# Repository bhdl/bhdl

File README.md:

# Board HDL: A Programming Language and System for making PCBs

Documents can be found at https://bhdl.org

This project is currently developed on a new IDE called CodePod, which is not publicly available yet. The `src` folder here is exported from CodePod IDE. We're working on making CodePod available for the general public. Issues are being tracked in this repo.

BHDL is a programming language embedded in
[racket](https://racket-lang.org/). In addition to the language, the system
consists of a layout co-design system based on functional picture, REPL-driven
interactive development and visualization, libraries, KiCAD compatible exporter,
and placement engines including an optimization-based anlytical placer (ePlace)
and simulated annealing based detailed placer.

# Setup

## Install Racket

Install [racket](https://racket-lang.org/):

```sh
apt install racket
```

On MacOS and Windows, you can [download the installer from the Racket website](https://download.racket-lang.org/), and setup
the commandline properly.

<!-- IMPORTANT: racket v7.8 seems to be broken! The cc-find will return negative values. That's apparently a bug of either racket v7.8 or the bundled pict library. Use v7.7 instead. Links to the download pages:

- [all versions](https://download.racket-lang.org/all-versions.html)
- [v7.7](https://download.racket-lang.org/racket-v7.7.html) -->

## Install BHDL package

Step 2: Install the BHDL directly as a racket package:

```
raco pkg install --auto https://github.com/bhdl/bhdl.git?path=src
```

You can now run racket and require bhdl. The first time requiring bhdl, it will download footprint library to `~/.config/bhdl/bhdl-footprints` (Linux) or `~/Library/Application Support/bhdl/bhdl-footprints` (MacOS).

```racket
racket
> (require bhdl)
```

Then try some of the [examples](/examples).

## Update BHDL

In the future, you can update the package if there're updates upstream via:

```shell
raco pkg update src
```

> note TODO package name should be `bhdl`

## JupyterLab IDE

In general, you can run racket programs via command line, editor plugins, IDEs. We are not covering them here. Instead, we recommand run the program via jupyter notebook. To set it up, first install jupyter:

```shell
pip install jupyterlab
```

The [iracket](https://github.com/rmculpepper/iracket) kernel requires on libzeromq:

```shell
sudo apt install libzmq5
```

> note for MacOS

> On MacOS, it is a little [trickier](https://github.com/rmculpepper/racket-zeromq/issues/6) to setup libzmq. Specifically, you need to copy the library to the racket's library path, otherwise racket won't find it:

> ```shell
> brew install zmq
> cp /opt/homebrew/Cellar/zeromq/4.3.4/lib/libzmq.5.dylib Library/Racket/8.2/lib
> ```

Then install the kernel itself:

```shell
raco pkg install iracket
raco iracket install
```

> note:
> iracket does not allow write access to file system by default. So you have to
> modify the kernel file with a [`-t`
> parameter](https://github.com/rmculpepper/iracket/issues/13). In short, you need
> to modify the content of `~/.local/share/jupyter/kernels/racket/kernel.json` on
> your system from `["racket","-l","iracket/iracket","--","{connection_file}"]` to
> `["racket","-l","iracket/iracket","--","-t","{connection_file}"]`

Then start the jupyterlab server:

```shell
jupyter lab
```

You'll be able to create racket notebooks in the JupyterLab IDE. Inside the
notebook, try `(require bhdl)` and some of [the exampels](/examples).

<!-- TODO rename fitboard to BHDL-Key -->

<!-- - [BHDL-Key](bhdl-test/fitboard.ipynb): an ergonomic keyboard
- [onebutton](bhdl-test/onebutton.ipynb): a pushbutton board: https://github.com/forrestbao/onebutton
- [Arduino Spreadboard](bhdl-test/spreadboard.ipynb): an multi-dock for different form-factor Arduinos -->

<!-- One caveat to notice: the iRacket kernel seems to have problem when "restarting the kernel". The walk-around is to "shutdown the kernel" and "start it again". -->

## Placement (Optional)

To run the placement engine, you need setup
[julia](https://julialang.org/). Refer to their installation guide on how to
install Julia.

Install the BHDL julia package:

```
julia
]add https://github.com/bhdl/bhdl
```

Then run the server:

```
import BHDL
BHDL.web_server()
```

This will listen on `http://0.0.0.0:8082`. To use this, in racket, set the
parameter `placer-url`, and call `circuit-export` with `#:auto-place #t`:

```racket
;; set placer url
(placer-url "http://0.0.0.0:8082")
(circuit-export three-button #:auto-place #t ...)
```

This package will detect if Nvidia GPU is available, and use it if possible. The
first time invoking the package, julia will download and instantiate the
dependencies and download CUDA (julia will not use your system's CUDA setup).
The first time the placement is running, Julia will pre-compile the code, thus
maybe a little slower. Subsequent placement request will be much faster (which
is why we use a server instead of invoking the command for every placement request).

## Freerouting (Optional)

To use routing, you need to have
[freerouting](https://github.com/freerouting/freerouting) available. We tested
on
[freerouting-v1.4.4](https://github.com/freerouting/freerouting/releases/tag/v1.4.4). Make
sure `freerouting-1.4.4-executable.jar` is available in your `$PATH`.

The executable can be downloaded [here](https://bintray.com/miho/Freerouting/download_file?file_path=eu%2Fmihosoft%2Ffreerouting%2Ffreerouting%2F1.4.4%2Ffreerouting-1.4.4-executable.jar) on the new freerouting maintainer website: https://freerouting.mihosoft.eu/

UPDATE: the jar file is often not an executable command. You'll need

```
java -jar freerouting-1.4.4-executable.jar
```

Thus, you need to create a executable called `freerouting`, containing:

```
#!/bin/bash
java -jar /path/to/freerouting-1.4.4-executable.jar
```

freerouting will need X11 window, even if we are running it in command line. Simulate the X11 session via:

```
sudo apt install xvfb
Xvfb :1
```

But it seems to be impossible to view the progress. We'll probably need to use VNC if we really want to know what's going on.

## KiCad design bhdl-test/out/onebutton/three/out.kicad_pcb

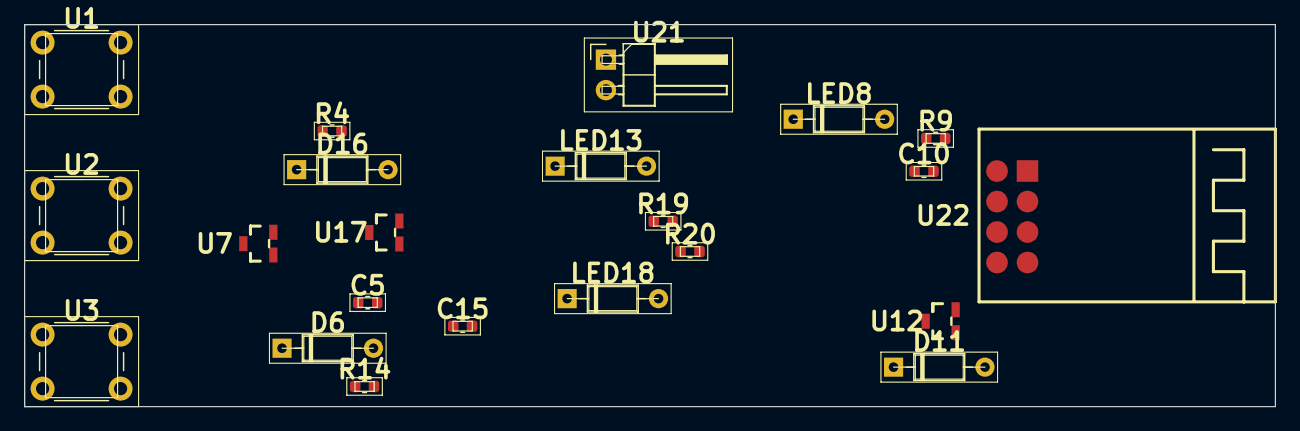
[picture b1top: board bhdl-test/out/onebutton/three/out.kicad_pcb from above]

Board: 2 copper layers, 104.2 x 31.8 mm, 22 parts (0 on the bottom side), 5 nets, no tracks yet.

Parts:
C5: C5
C10: C10
C15: C15
D6: D6
D11: D11
D16: D16
LED8: LED8
LED13: LED13
LED18: LED18
R4: R4
R9: R9
R14: R14
R19: R19
R20: R20
U1: U1
U2: U2
U3: U3
U7: U7
U12: U12
U17: U17
U21: U21
U22: U22

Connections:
1: C15.1, C15.2, D16.1, R14.2, U17.3
2: LED8.1, LED8.2, LED13.1, LED13.2, LED18.1, LED18.2, R19.1, R19.2, R20.1, R20.2, U7.1, U12.1, U17.1, U21.1, U22.1, U22.2, U22.3
3: C5.1, C5.2, D6.1, R4.2, U7.3
4: D6.2, D11.2, D16.2, R4.1, R9.1, R14.1, U1.1, U1.2, U2.1, U2.2, U3.1, U3.2, U21.2, U22.8
5: C10.1, C10.2, D11.1, R9.2, U12.3

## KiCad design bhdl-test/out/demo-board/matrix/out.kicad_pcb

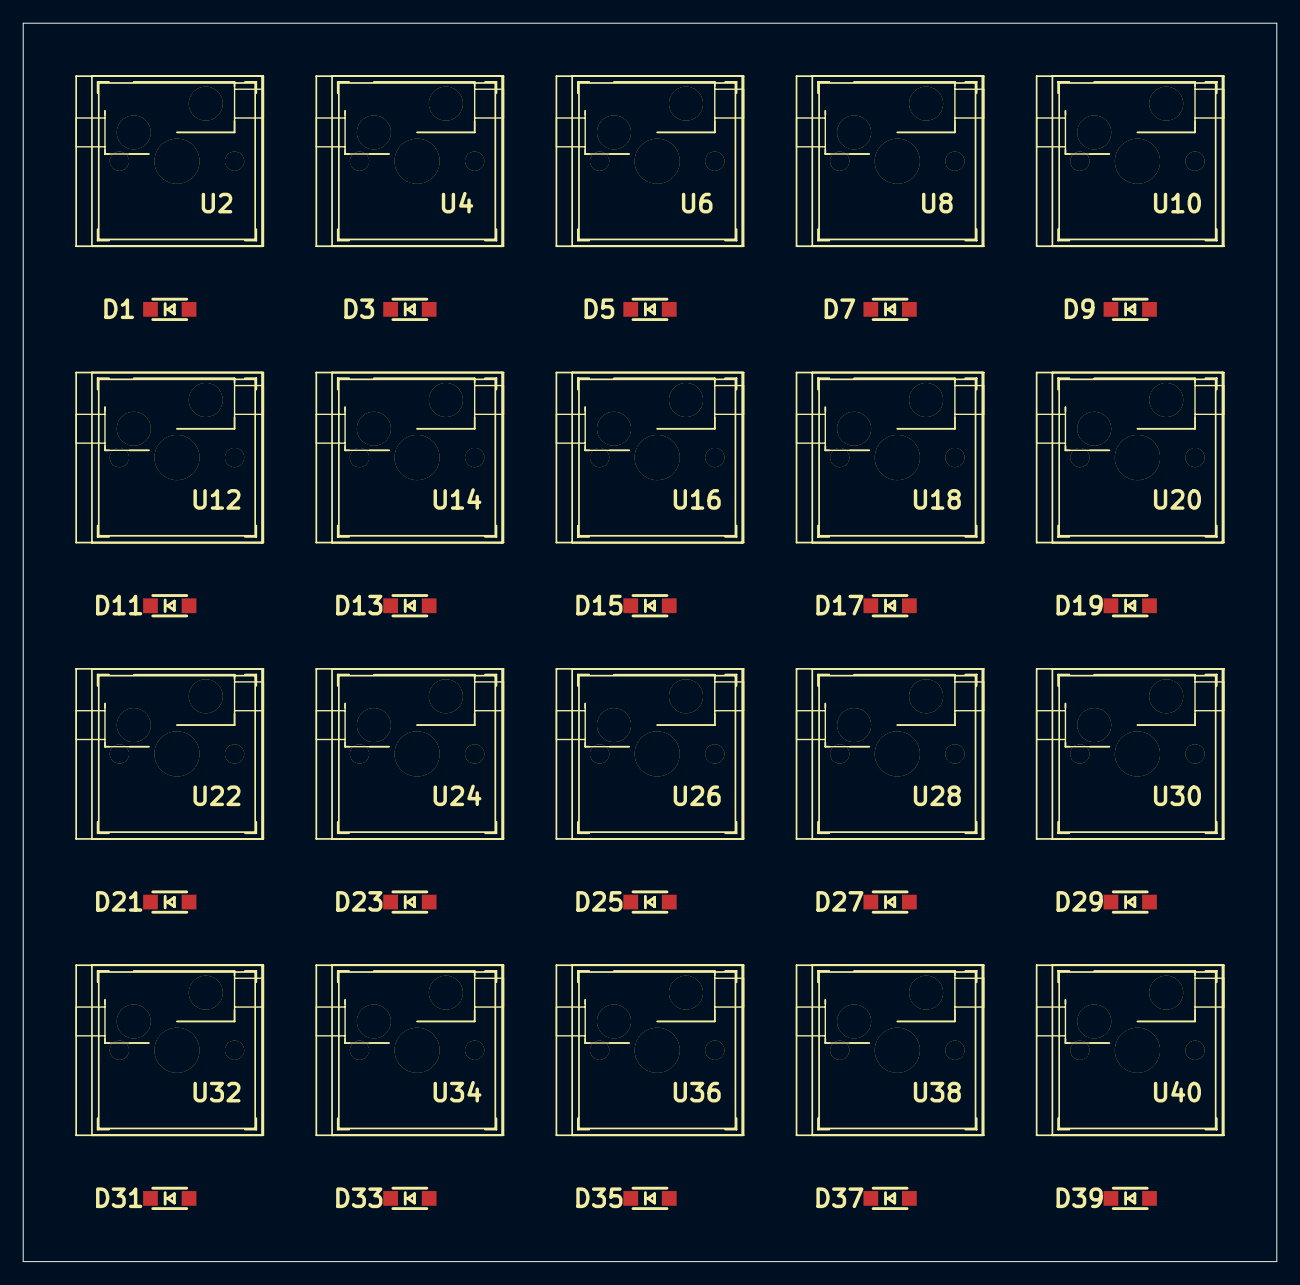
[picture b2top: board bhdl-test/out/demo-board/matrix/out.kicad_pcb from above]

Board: 2 copper layers, 110.6 x 109.2 mm, 40 parts (0 on the bottom side), 29 nets, no tracks yet.

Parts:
D1: D1
D3: D3
D5: D5
D7: D7
D9: D9
D11: D11
D13: D13
D15: D15
D17: D17
D19: D19
D21: D21
D23: D23
D25: D25
D27: D27
D29: D29
D31: D31
D33: D33
D35: D35
D37: D37
D39: D39
U2: U2
U4: U4
U6: U6
U8: U8
U10: U10
U12: U12
U14: U14
U16: U16
U18: U18
U20: U20
U22: U22
U24: U24
U26: U26
U28: U28
U30: U30
U32: U32
U34: U34
U36: U36
U38: U38
U40: U40

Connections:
1: D1.1, U2.2
2: D39.1, U40.2
3: D37.1, U38.2
4: D1.2, D3.2, D5.2, D7.2, D9.2
5: D7.1, U8.2
6: D23.1, U24.2
7: D3.1, U4.2
8: D33.1, U34.2
9: D29.1, U30.2
10: D11.1, U12.2
11: D9.1, U10.2
12: U8.1, U18.1, U28.1, U38.1
13: D19.1, U20.2
14: D17.1, U18.2
15: D31.1, U32.2
16: D35.1, U36.2
17: D13.1, U14.2
18: U2.1, U12.1, U22.1, U32.1
19: D11.2, D13.2, D15.2, D17.2, D19.2
20: D25.1, U26.2
21: D21.2, D23.2, D25.2, D27.2, D29.2
22: U6.1, U16.1, U26.1, U36.1
23: D31.2, D33.2, D35.2, D37.2, D39.2
24: D21.1, U22.2
25: U10.1, U20.1, U30.1, U40.1
26: D27.1, U28.2
27: D15.1, U16.2
28: D5.1, U6.2
29: U4.1, U14.1, U24.1, U34.1

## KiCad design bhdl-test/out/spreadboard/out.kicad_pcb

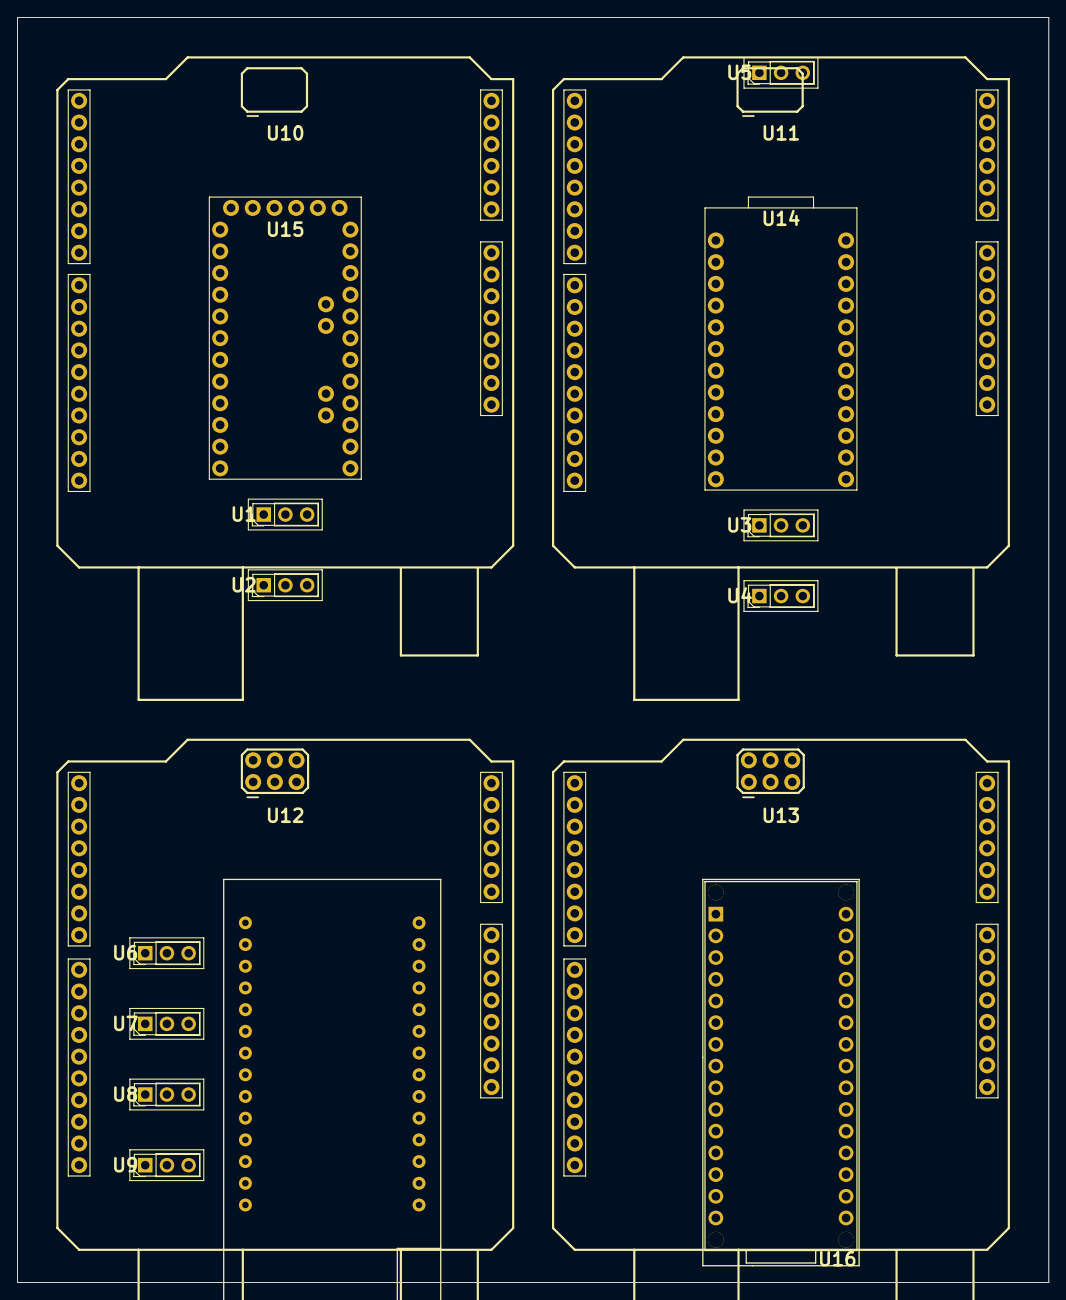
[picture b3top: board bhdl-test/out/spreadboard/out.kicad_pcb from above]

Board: 2 copper layers, 120.7 x 148.0 mm, 17 parts (0 on the bottom side), 37 nets, no tracks yet.

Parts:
U1: U1
U2: U2
U3: U3
U4: U4
U5: U5
U6: U6
U7: U7
U8: U8
U9: U9
U10: U10
U11: U11
U12: U12
U13: U13
U14: U14
U15: U15
U16: U16
U17: U17

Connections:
1: U2.2, U15.A4, U16.A4
2: U10.D10, U11.D10, U12.D10, U13.D10, U14.13, U15.13, U16.D10, U17.19
3: U7.2, U17.18
4: U12.5V_I, U13.5V_I
5: U6.1, U10.D8, U11.D8, U12.D8, U13.D8, U14.11, U15.11, U16.D8
6: U3.1, U10.D2, U11.D2, U12.D2, U13.D2, U15.5, U16.D2, U17.11
7: U16.D1, U17.10
8: U6.2, U17.17
9: U15.A7, U16.A7
10: U10.D5, U11.D5, U12.D5, U13.D5, U14.8, U15.8, U16.D5, U17.14
11: U5.2, U14.21, U15.21
12: U1.3, U4.3, U9.3, U10.SCL
13: U3.2, U14.5
14: U9.2, U17.21
15: U7.1, U10.D9, U11.D9, U12.D9, U13.D9, U14.12, U15.12, U16.D9
16: U7.3, U10.D13, U11.D13, U12.D13, U12.SCK, U13.D13, U13.SCK, U15.16, U16.D13, U17.22
17: U2.3, U3.3, U8.3, U10.SDA
18: U16.D0, U17.9
19: U15.A6, U16.A6, U17.8
20: U1.1, U10.A5, U11.A5, U12.A5, U13.A5, U17.7
21: U10.A0, U11.A0, U12.A0, U13.A0, U14.17, U15.17, U16.A0, U17.2
22: U10.D4, U11.D4, U12.D4, U13.D4, U14.7, U15.7, U16.D4, U17.13
23: U1.2, U15.A5, U16.A5
24: U5.1, U10.3.3V, U11.3.3V, U12.3.3V, U13.3.3V, U16.3V3, U17.26
25: U10.A1, U11.A1, U12.A1, U13.A1, U14.18, U15.18, U16.A1, U17.3
26: U2.1, U10.A4, U11.A4, U12.A4, U13.A4, U17.6
27: U10.A3, U11.A3, U12.A3, U13.A3, U14.20, U15.20, U16.A3, U17.5
28: U10.A2, U11.A2, U12.A2, U13.A2, U14.19, U15.19, U16.A2, U17.4
29: U9.1, U10.D12, U11.D12, U12.D12, U12.MISO, U13.D12, U13.MISO, U15.15, U16.D12
30: U8.2, U17.20
31: U5.3, U10.5V, U11.5V, U12.5V, U13.5V, U16.5V, U17.28
32: U10.GND@, U11.GND@, U12.GND@, U12.GND_, U13.GND@, U13.GND_, U14.3, U14.4, U14.23, U15.4, U15.23, U16.GND1, U16.GND2, U17.25
33: U4.1, U10.D3, U11.D3, U12.D3, U13.D3, U15.6, U16.D3, U17.12
34: U4.2, U14.6
35: U10.D7, U11.D7, U12.D7, U13.D7, U14.10, U15.10, U16.D7, U17.16
36: U10.D6, U11.D6, U12.D6, U13.D6, U14.9, U15.9, U16.D6, U17.15
37: U6.3, U8.1, U10.D11, U11.D11, U12.D11, U12.MOSI, U13.D11, U13.MOSI, U15.14, U16.D11

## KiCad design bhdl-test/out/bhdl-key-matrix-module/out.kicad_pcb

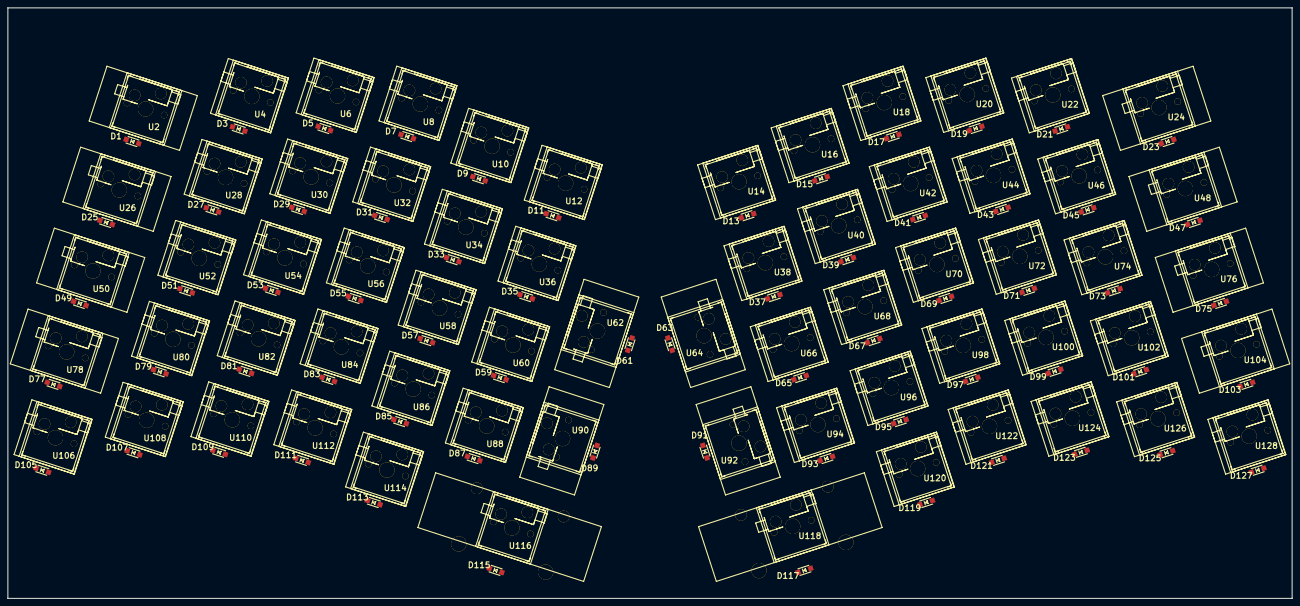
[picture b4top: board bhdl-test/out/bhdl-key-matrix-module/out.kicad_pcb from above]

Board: 2 copper layers, 334.5 x 153.8 mm, 128 parts (0 on the bottom side), 83 nets, no tracks yet.

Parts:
D1: D1
D3: D3
D5: D5
D7: D7
D9: D9
D11: D11
D13: D13
D15: D15
D17: D17
D19: D19
D21: D21
D23: D23
D25: D25
D27: D27
D29: D29
D31: D31
D33: D33
D35: D35
D37: D37
D39: D39
D41: D41
D43: D43
D45: D45
D47: D47
D49: D49
D51: D51
D53: D53
D55: D55
D57: D57
D59: D59
D61: D61
D63: D63
D65: D65
D67: D67
D69: D69
D71: D71
D73: D73
D75: D75
D77: D77
D79: D79
D81: D81
D83: D83
D85: D85
D87: D87
D89: D89
D91: D91
D93: D93
D95: D95
D97: D97
D99: D99
D101: D101
D103: D103
D105: D105
D107: D107
D109: D109
D111: D111
D113: D113
D115: D115
D117: D117
D119: D119
D121: D121
D123: D123
D125: D125
D127: D127
U2: U2
U4: U4
U6: U6
U8: U8
U10: U10
U12: U12
U14: U14
U16: U16
U18: U18
U20: U20
U22: U22
U24: U24
U26: U26
U28: U28
U30: U30
U32: U32
U34: U34
U36: U36
U38: U38
U40: U40
U42: U42
U44: U44
U46: U46
U48: U48
U50: U50
U52: U52
U54: U54
U56: U56
U58: U58
U60: U60
U62: U62
U64: U64
U66: U66
U68: U68
U70: U70
U72: U72
U74: U74
U76: U76
U78: U78
U80: U80
U82: U82
U84: U84
U86: U86
U88: U88
U90: U90
U92: U92
U94: U94
U96: U96
U98: U98
U100: U100
U102: U102
U104: U104
U106: U106
U108: U108
U110: U110
U112: U112
U114: U114
U116: U116
U118: U118
U120: U120
U122: U122
U124: U124
U126: U126
U128: U128

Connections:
1: D9.1, U10.2
2: D77.2, D79.2, D81.2, D83.2, D85.2, D87.2, D89.2, D91.2, D93.2, D95.2, D97.2, D99.2, D101.2, D103.2
3: D117.1, U118.2
4: D25.1, U26.2
5: D45.1, U46.2
6: D107.1, U108.2
7: D33.1, U34.2
8: D27.1, U28.2
9: U2.1, U26.1, U50.1, U78.1, U106.1
10: D23.1, U24.2
11: D87.1, U88.2
12: U20.1, U44.1, U72.1, U100.1, U124.1
13: D47.1, U48.2
14: D35.1, U36.2
15: D115.1, U116.2
16: D5.1, U6.2
17: D101.1, U102.2
18: D121.1, U122.2
19: D57.1, U58.2
20: U8.1, U32.1, U56.1, U84.1, U112.1
21: D17.1, U18.2
22: U62.1, U90.1
23: D85.1, U86.2
24: D99.1, U100.2
25: D77.1, U78.2
26: U24.1, U48.1, U76.1, U104.1, U128.1
27: D1.1, U2.2
28: D11.1, U12.2
29: D37.1, U38.2
30: D49.1, U50.2
31: D25.2, D27.2, D29.2, D31.2, D33.2, D35.2, D37.2, D39.2, D41.2, D43.2, D45.2, D47.2
32: D3.1, U4.2
33: D91.1, U92.2
34: D19.1, U20.2
35: D43.1, U44.2
36: D29.1, U30.2
37: D69.1, U70.2
38: U16.1, U40.1, U68.1, U96.1, U120.1
39: D125.1, U126.2
40: D103.1, U104.2
41: D89.1, U90.2
42: D113.1, U114.2
43: D51.1, U52.2
44: D67.1, U68.2
45: U12.1, U36.1, U60.1, U88.1, U116.1
46: D79.1, U80.2
47: U22.1, U46.1, U74.1, U102.1, U126.1
48: D119.1, U120.2
49: D1.2, D3.2, D5.2, D7.2, D9.2, D11.2, D13.2, D15.2, D17.2, D19.2, D21.2, D23.2
50: D95.1, U96.2
51: D39.1, U40.2
52: D13.1, U14.2
53: D7.1, U8.2
54: D93.1, U94.2
55: D31.1, U32.2
56: D75.1, U76.2
57: D97.1, U98.2
58: D49.2, D51.2, D53.2, D55.2, D57.2, D59.2, D61.2, D63.2, D65.2, D67.2, D69.2, D71.2, D73.2, D75.2
59: D53.1, U54.2
60: U64.1, U92.1
61: D127.1, U128.2
62: D105.1, U106.2
63: D73.1, U74.2
64: D83.1, U84.2
65: U4.1, U28.1, U52.1, U80.1, U108.1
66: D21.1, U22.2
67: U10.1, U34.1, U58.1, U86.1, U114.1
68: D123.1, U124.2
69: D63.1, U64.2
70: D41.1, U42.2
71: U14.1, U38.1, U66.1, U94.1, U118.1
72: D59.1, U60.2
73: D55.1, U56.2
74: D61.1, U62.2
75: D15.1, U16.2
76: D109.1, U110.2
77: D111.1, U112.2
78: D81.1, U82.2
79: D105.2, D107.2, D109.2, D111.2, D113.2, D115.2, D117.2, D119.2, D121.2, D123.2, D125.2, D127.2
80: D65.1, U66.2
81: U18.1, U42.1, U70.1, U98.1, U122.1
82: D71.1, U72.2
83: U6.1, U30.1, U54.1, U82.1, U110.1

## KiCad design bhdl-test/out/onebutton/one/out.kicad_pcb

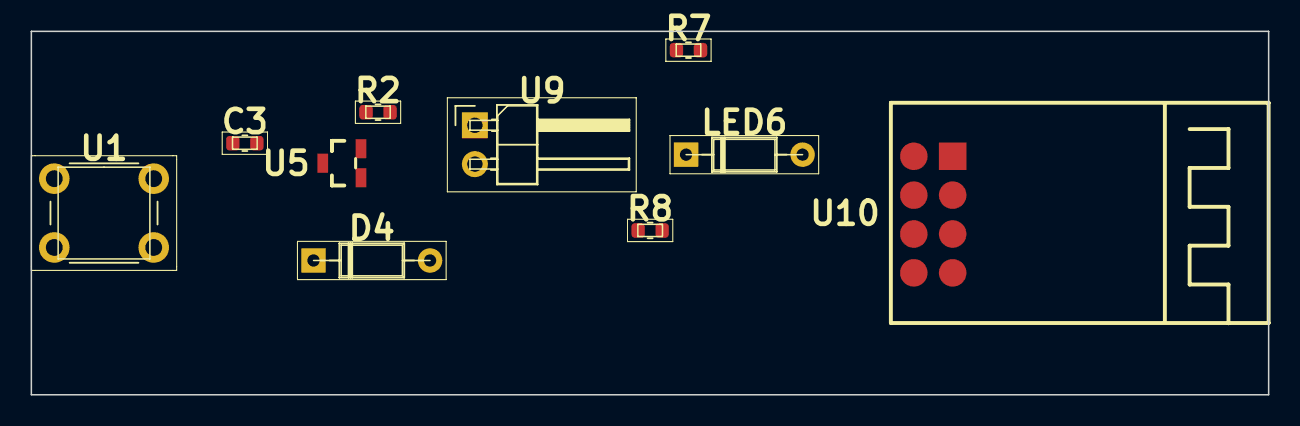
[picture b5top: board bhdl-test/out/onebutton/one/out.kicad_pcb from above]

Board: 2 copper layers, 80.9 x 23.8 mm, 10 parts (0 on the bottom side), 3 nets, no tracks yet.

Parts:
C3: C3
D4: D4
LED6: LED6
R2: R2
R7: R7
R8: R8
U1: U1
U5: U5
U9: U9
U10: U10

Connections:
1: D4.2, R2.1, U1.1, U1.2, U9.2, U10.8
2: C3.1, C3.2, D4.1, R2.2, U5.3
3: LED6.1, LED6.2, R7.1, R7.2, R8.1, R8.2, U5.1, U9.1, U10.1, U10.2, U10.3

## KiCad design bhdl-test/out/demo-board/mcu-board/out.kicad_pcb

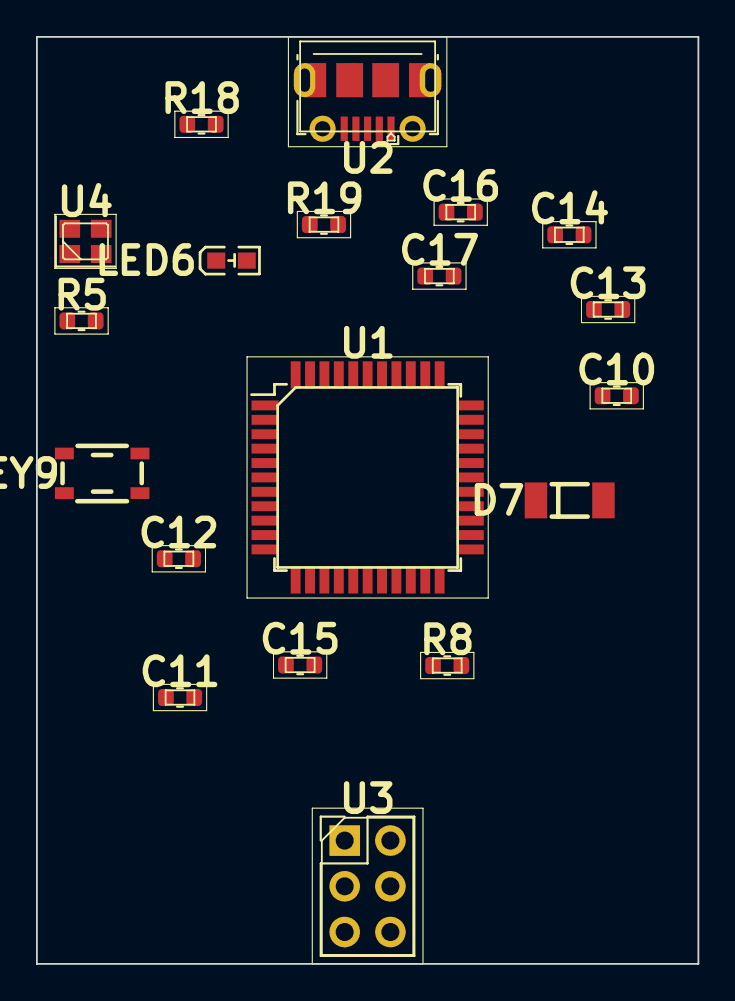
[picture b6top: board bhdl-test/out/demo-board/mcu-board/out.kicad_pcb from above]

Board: 2 copper layers, 36.7 x 51.5 mm, 19 parts (0 on the bottom side), 16 nets, no tracks yet.

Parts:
C10: C10
C11: C11
C12: C12
C13: C13
C14: C14
C15: C15
C16: C16
C17: C17
D7: D7
KEY9: KEY9
LED6: LED6
R5: R5
R8: R8
R18: R18
R19: R19
U1: U1
U2: U2
U3: U3
U4: U4

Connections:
1: U1.11, U3.1
2: C17.1, U1.16, U4.3
3: U1.10, U3.4
4: D7.2, KEY9.1, R8.1, U1.13, U3.5
5: R18.2, U2.3
6: R18.1, U1.4
7: U1.9, U3.3
8: R5.1, U1.31
9: LED6.2, R5.2
10: C11.1, C12.1, C13.1, C14.1, C15.1, U1.2, U1.7, U1.14, U1.24, U1.34, U1.44, U2.1, U3.2
11: C16.1, U1.17, U4.1
12: C10.1, U1.6
13: R19.2, U2.2
14: D7.1, R8.2
15: R19.1, U1.3
16: C10.2, C11.2, C12.2, C13.2, C14.2, C15.2, C16.2, C17.2, KEY9.3, LED6.1, U1.5, U1.15, U1.23, U1.35, U1.43, U2.5, U3.6, U4.2, U4.4

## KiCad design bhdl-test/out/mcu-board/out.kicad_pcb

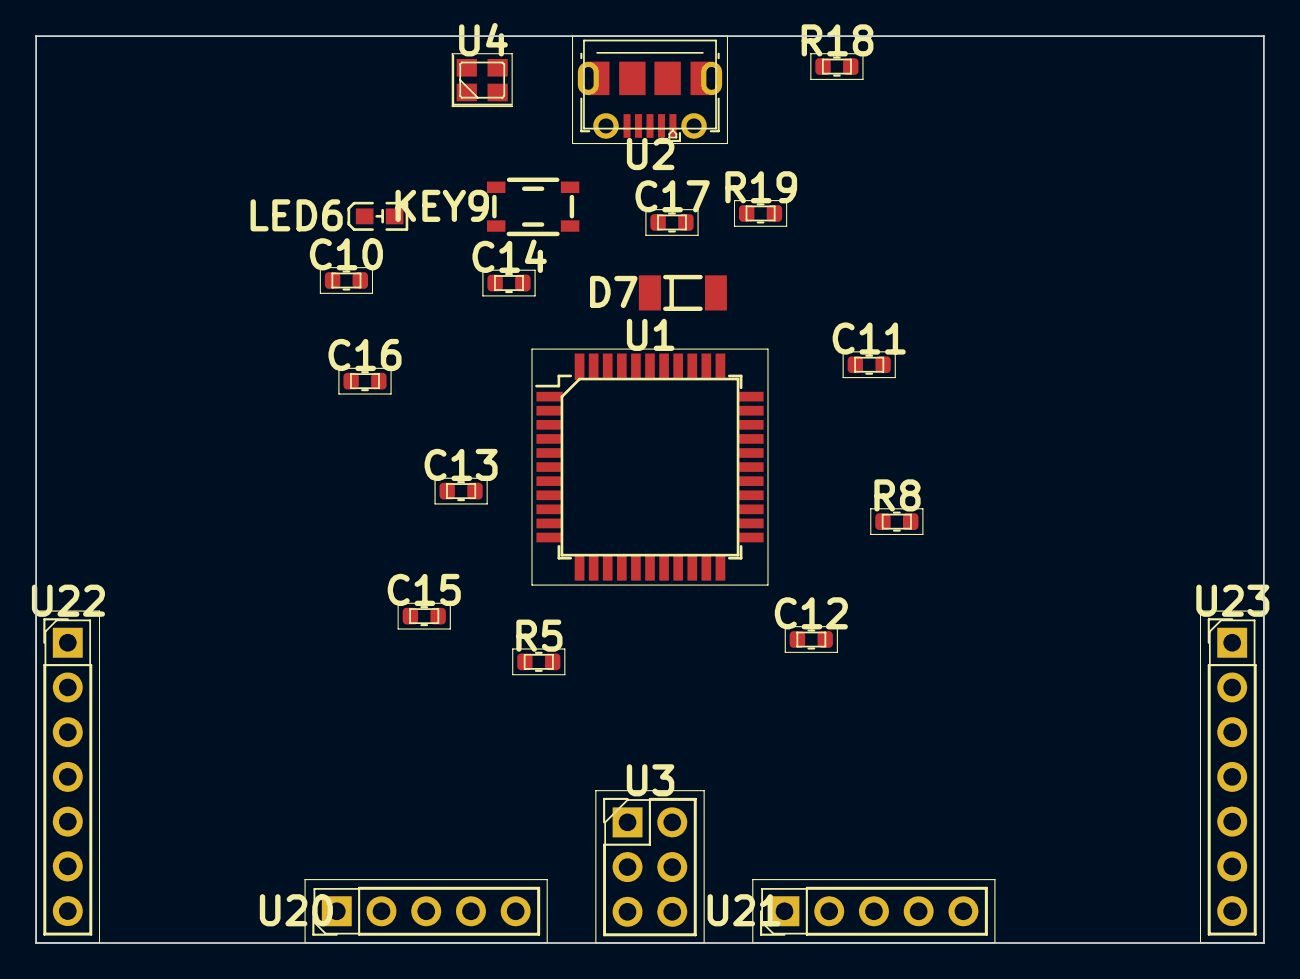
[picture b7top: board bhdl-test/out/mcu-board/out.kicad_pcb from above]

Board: 2 copper layers, 69.7 x 51.5 mm, 23 parts (0 on the bottom side), 35 nets, no tracks yet.

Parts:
C10: C10
C11: C11
C12: C12
C13: C13
C14: C14
C15: C15
C16: C16
C17: C17
D7: D7
KEY9: KEY9
LED6: LED6
R5: R5
R8: R8
R18: R18
R19: R19
U1: U1
U2: U2
U3: U3
U4: U4
U20: U20
U21: U21
U22: U22
U23: U23

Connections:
1: U1.8, U20.1, U21.1
2: U1.29, U20.3, U21.3
3: C17.1, U1.16, U4.3
4: U1.9, U3.3
5: U1.30, U20.4, U21.4
6: U1.37, U23.6
7: U1.11, U3.1
8: U1.40, U23.3
9: U1.36, U23.7
10: U1.18, U22.1
11: U1.39, U23.4
12: U1.27, U23.1
13: U1.19, U22.2
14: U1.28, U20.2, U21.2
15: U1.10, U3.4
16: R19.1, U1.3
17: U1.22, U22.6
18: C16.1, U1.17, U4.1
19: U1.41, U23.2
20: U1.25, U22.5
21: U1.21, U22.4
22: D7.1, R8.2
23: R19.2, U2.2
24: D7.2, KEY9.1, R8.1, U1.13, U3.5
25: R5.1, U1.31
26: R18.2, U2.3
27: C11.1, C12.1, C13.1, C14.1, C15.1, U1.2, U1.7, U1.14, U1.24, U1.34, U1.44, U2.1, U3.2
28: U1.26, U22.7
29: U1.20, U22.3
30: U1.38, U23.5
31: C10.1, U1.6
32: LED6.2, R5.2
33: C10.2, C11.2, C12.2, C13.2, C14.2, C15.2, C16.2, C17.2, KEY9.3, LED6.1, U1.5, U1.15, U1.23, U1.35, U1.43, U2.5, U3.6, U4.2, U4.4
34: R18.1, U1.4
35: U1.12, U20.5, U21.5

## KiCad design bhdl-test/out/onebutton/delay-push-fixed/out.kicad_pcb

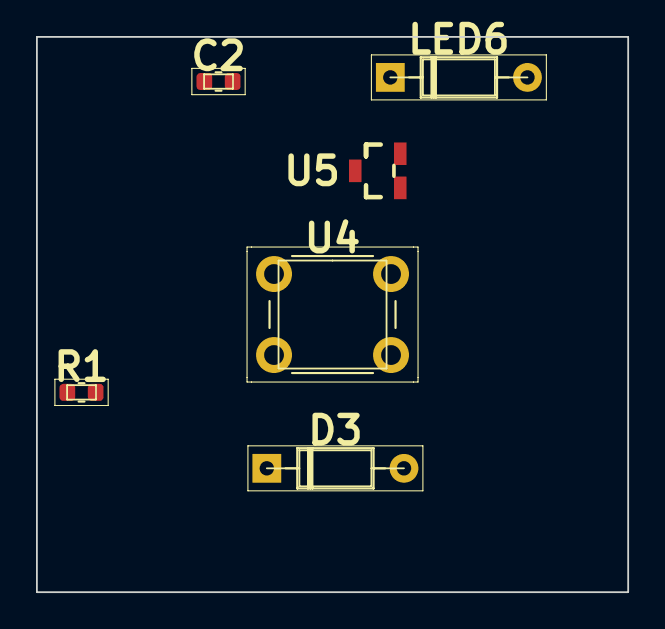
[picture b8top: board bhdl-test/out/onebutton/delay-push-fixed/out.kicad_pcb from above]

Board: 2 copper layers, 32.8 x 30.8 mm, 6 parts (0 on the bottom side), 3 nets, no tracks yet.

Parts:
C2: C2
D3: D3
LED6: LED6
R1: R1
U4: U4
U5: U5

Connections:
2: LED6.2, U5.1
3: D3.2, R1.1, U4.1, U4.2
4: C2.1, C2.2, D3.1, R1.2, U5.3

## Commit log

2019-08-06 init
2019-08-08 finish schematic and footprint
2019-08-09 add gerber format doc
2019-08-09 add pict & locs to symbol & footprint; add symbol & footprint to IC
2019-08-10 unify sch-symbol and footprint struct; add ATMEGA328P and ATMEGA16U2
2019-08-12 Add kicad footprint reader and gerber generator
2019-08-14 add gerber viewer
2019-08-15 new abstraction of footprint
2019-08-15 clean up documents
2019-08-18 half-way in footprint-library; many fixes in footprint->pict
2019-08-18 finish all kicad footprints
2019-08-19 footprint->gerber use closure for aperture selection
2019-08-21 add connect macro
2019-08-21 add IC->gerber and IC->pict
2019-08-23 add Spectra doc
2019-08-25 add IC->airwires
2019-12-28 use ~/git/ path
2019-12-28 add business card code
2019-12-28 move usb to library.rkt
2019-12-28 add uno
2020-01-20 rework business card
2020-02-04 remove hard-coded path
2020-02-13 clean up notes
2020-02-20 add symbol.rkt and symbol-library.rkt
2020-02-23 add locs information to symbol
2020-02-23 new schematic with netlist exporting
2020-02-23 backup old schematic.rkt
2020-02-23 use new schematic.rkt
2020-02-24 finish hook macro, dot-notation
2020-02-24 notes on auto-placer
2020-02-24 adjust netlist export format
2020-03-16 add lef/def notes
2020-03-16 read ISPD 05/06 benchmarks
2020-03-16 add visualization
2020-03-16 ignore png files
2020-03-19 add placement framework
2020-04-01 add lef parser
2020-04-01 add def parser
2020-04-02 add lefdef visualization
2020-04-03 add schematic lef/def export
2020-04-13 refactor sch,sch-lib,test-sch; add send-for-placement
2020-04-13 alternative julia syntax
2020-04-13 finish place for PCB scale; add server
2020-04-13 update notes
2020-04-13 refactor dir arch
2020-04-18 unified struct for sch and place; finish racket vis for place result
2020-04-18 update jl packages
2020-04-18 read data directly xs,ys,ws,hs; adapt hparams for PCB scale; return shifted solxs/ys
2020-04-25 notes
2020-04-25 refactor fp and symbol and their libs; clean up gerber.rkt; test dir
2020-04-28 finish parsec for one DEF/p
2020-04-28 finish lexer + parsec
2020-04-29 add kicad-symbol visualization
2020-04-29 unified library from scratch
2020-04-30 add IC->symbol-pict; refactor library-io/raw/syntax.rkt
2020-04-30 use define-alias in IC def; add more ICs
2020-04-30 finish library-syntax.rkt
2020-04-30 deprecate library-raw.rkt
2020-04-30 deprecate symbol-library.rkt and symbol-kicad.rkt
2020-04-30 notes about footprints
2020-05-04 add compose-pipe; and use it to refactor rect-symbol->pict+locs
2020-05-04 add compose-pipe document
2020-05-05 finish IC->symbol-pict
2020-05-05 fp-kicad add contracts
2020-05-05 finish IC->footprint and IC->symbol in library-io.rkt
2020-05-05 unify libraries
2020-05-05 placement for both symbol and fp
2020-05-06 fix fp pad locs
2020-05-06 kicad fp library pad filters string names; fp package default to #f
2020-05-06 remove PAD in QFN kicad fp
2020-05-06 upcase all ICs
2020-05-06 use NamedPoint to sort locs in atom->XXX-pict+locs
2020-05-06 rename ATMEGA8U2 to ATmega8U2
2020-05-07 add hook!
2020-05-07 finish uno whole-board
2020-05-07 deprecate uno.rkt
2020-05-07 use new uno definition as uno.rkt
2020-05-07 add report-20200507
2020-05-07 fix pdf link
2020-05-07 use relative file path
2020-05-09 add gh60; add fixed loc; add in-place part; add *- and *< syntax
2020-05-11 cherry switch fp for gh60
2020-05-12 remove fixed diearea; fix fixed loc mismatch; use real fp size
2020-05-12 increase wirelength weight
2020-05-13 move back folder out of src/
2020-05-13 Add struct Net and support weights
2020-05-13 remove schematic symbol support; add USB
2020-05-13 add kicad_pcb exporting
2020-06-20 pkg upgrade
2020-06-20 notes and profiling
2020-06-20 fix some naming conflicts
2020-06-28 use define-Composite sytnax; use picted-Atom instead of loced-Atom
2020-06-28 notes, packages, precompile
2020-06-28 do not use @threads; speed up placement by using GPU for rho_cell
2020-06-29 add SA legalization
2020-06-29 fix scale and corner/center coordinate for kicad pcb export
2020-06-29 map to valid region in legalization
2020-06-30 add UUID reference for kicad_pcb export
2020-06-30 fix mismatch due to fp origin; remove explicit diearea
2020-06-30 support hyper-params in send-for-placement
2020-06-30 picted-atoms! with optional pict
2020-07-01 add Composite->dsn and freerouting system call
2020-07-10 add splicing syntax ..; switch spacing; *-append for Atom; use #:vars and #:layout
2020-07-10 save-file respects filename extension
2020-07-10 initial placement to middle
2020-07-10 add fitboard
2020-07-10 some backup code
2020-07-10 add rotate support for fixed location atoms
2020-07-11 add rotation in detailed placement; add seed! for placement
2020-07-11 add a version of HBKB that places diode at fixed location
2020-07-12 add Arduino libraries
2020-07-12 wrap-*-superimpose
2020-07-12 fix Arduino library pinnames
2020-07-12 fix origin == center NaN issue
2020-07-12 add vectorized connection syntax
2020-07-12 add spreadboard
2020-07-13 organize into racket package
2020-07-13 add BHDL_KICAD_FOOTPRINT_PATH env var
2020-07-13 add *+ syntax
2020-07-13 add documents
2020-07-13 simplify racket pkg install notes
2020-07-14 remove picted-atom!, add maybe-find; add make-Composite
2020-07-14 add local pkg install instruction
2020-07-15 add fuse example PNG
2020-07-15 fix fuse.rkt
2020-07-15 expose define/IC for user-defined components
2020-07-15 remove edge weight
2020-07-15 fix *+-proc; remove hook and hook!
2020-07-17 Create a dual-fuse PCB
2020-07-23 add easycad reader; add fp-esp32-wrover-e
2020-07-23 add LQFP
2020-07-23 consider flash pad size for bounding-box
2020-07-23 add GD32VF103CBT6 and ESP32-WROVER-E
2020-07-23 use syntax-parameter for self
2020-07-23 add numeric pins for make-Composite
2020-07-23 fix key-with-code var name and external pins
2020-07-29 add missing fp; define/IC defines IC:XXX and XXX; hide make-IC-atom
2020-07-29 add esp32 and gd32 MCUs
2020-07-29 add bhdl-footprints submodule
2020-07-29 separate fp-easyeda.rkt
2020-07-29 use private dir
2020-07-29 wrap inset; use make-circuit; add circuit-export
2020-07-29 add name field to IC and use that in KiCAD export
2020-07-29 maybe-find return list instead of values
2020-07-29 fix pin name
2020-07-29 remove net weight
2020-07-29 remove filtering of 1-size net
2020-07-29 add lcsc->fp uuid->fp lcsc->uuid
2020-07-29 add warn and debug
2020-07-29 clean up spreadboard.rkt
2020-07-29 re-enable (pin-ref self yname)
2020-07-29 easyeda docs
2020-07-29 update submodule
2020-07-30 pad-spec use name instead of index
2020-07-30 FpSpec add name and fp selection support; param PinHeader and Cherry
2020-07-30 add assert
2020-07-30 library-io support which-fp
2020-07-30 remove combine-Composites; use left and right; fix netlist
2020-07-30 add missing require
2020-07-30 adjust fitboard and spreadboard with updated syntax
2020-07-31 fix place-spec mask computation
2020-07-31 add cache for place-result
2020-07-31 IC prefix
2020-07-31 add parse-rect for EasyEDA; support pad-with-hole for KiCAD
2020-07-31 add LED0603 and 1N4148W; add some prefixes
2020-07-31 fix dsn net pads
2020-07-31 place SoCs buttons LEDs USBs for fitboard
2020-07-31 do not move fixed atoms into valid region
2020-07-31 break when no conflicts
2020-07-31 fix thru_hole and smd pads in kicad an dsn export
2020-07-31 use 0.127 for KiCAD DRC
2020-07-31 use clipper for conflict detection
2020-08-04 add 4-layer board template
2020-08-04 add extra spacing for component footprint
2020-08-04 fix nul
2020-08-04 save place-spec.json during export
2020-08-04 ignore ipynb checkpoints
2020-08-07 footprint library use BHDL_LIBRARY_PATH
2020-08-07 make dir if not exist
2020-08-07 use shell instead of system
2020-08-07 separate fitboard-lib.rkt
2020-08-07 add fitboard.ipynb
2020-08-08 use port 8082 for placement
2020-08-08 update julia packages
2020-08-08 use README.md
2020-08-08 separate documents
2020-08-08 use #:ALIAS instead of #:ALTS
2020-08-08 multiple FPs for resistor
2020-08-08 add show-layout
2020-08-08 add note
2020-08-08 add iracket and BHDL setup
2020-08-09 add padding-general
2020-08-09 remove filk screen for THT hole
2020-08-09 add edge cut
2020-08-09 fix show-layout
2020-08-09 not using bhdl/splicing
2020-08-10 add racket for code block
2020-08-17 fitboard notebook with placement
2020-08-17 place engine clean output; use jupyter visualization
2020-08-17 placement server notebook
2020-08-17 playground notebooks
2020-08-17 docs
2020-08-21 add pinheader2 and kailh socket
2020-08-21 circuit-export return pict
2020-08-21 compute conflict skip fixed atoms
2020-08-21 add fitboard-lite
2020-08-25 add parse-hole support
2020-08-27 sep holes; add fp layer support; fix drill; add kailh socket unit support;
2020-08-27 use kailh socket
2020-08-27 playgrounds
2020-09-11 show text on SilkS
2020-09-11 fix atom orders
2020-09-11 replace CuArrays with CUDA
2020-09-11 custom print Atom
2020-09-11 support text-spec for text position
2020-09-11 add pin name to KiCAD export
2020-09-11 fix a pin alt
2020-09-11 add modular design
2020-09-11 clean up notebooks
2020-09-11 ignore some racket cache
2020-09-11 add stabilizer and mounting holes
2020-09-12 Add pad rotation support; add hash-ref-ref-noerr; add half-mat; fp-kicad support pad layer
2020-09-12 update bhdl-footprints
2020-09-21 Add attrs for BOM export; update USB micro
2020-09-21 Remove ProfileView
2020-09-21 Fix ICSP header; use MicroUSB; fix crystal footprint and connection
2020-09-21 Add debug pin/pad names
2020-09-21 Increase text font for spreadboard
2020-09-21 Fix Arduino ICs
2020-09-21 Add spreadboard notebook
2020-09-22 Remove old fitboard.ipynb
2020-09-22 Rename fitboard-lite to fitboard
2020-09-22 remove IC-name/pin/pad debugging info
2020-09-22 Add circuit-plot
2020-09-22 support vector pins and connections
2020-09-22 add demo-board; use vector pins for col/cow in notebooks
2020-09-22 add PNG/SVG export
2020-09-22 new documents with getting started
2020-09-22 add rebellion deps
2020-09-22 auto-place #f for spreadboard
2020-09-26 Add jupyter kernel setup
2020-10-29 export kicad->fp
2020-10-29 add anode cathode; export define/IC
2020-10-29 use match-let* for #:vars
2020-10-29 add onebutton
2020-10-29 racket install instructions
2020-10-29 rename fitboard to BHDL-Key
2020-10-29 update links to demo boards
2020-10-29 remove old .rkt files
2020-10-29 add onebutton outputs
2020-10-30 replace ellipse to oval in easyeda pads
2020-10-30 add doc about placement engine
2020-10-30 use version 5 for KiCAD export
2020-10-30 add onebutton KiCAD output files
2020-11-06 add placement management inside racket
2020-11-06 use 8082 for placement process management
2020-11-06 add output for all notebooks
2020-11-06 add all kicad_pcb output files
2020-12-08 fix several connection issues
2021-05-23 add devcontainer
2021-05-23 add julia and fix permission for dev container
2021-05-25 add jupyterlab plugins
2021-06-06 racket 7.7
2021-06-06 use racket v8.1
2021-06-15 install latest pict
2021-06-16 separate docker image into bhdl and placer
2021-06-16 package update
2021-06-16 listen to 0.0.0.0; instantiate pkg in main.jl
2021-06-16 add placer-url
2021-06-16 add lsof pkg
2021-06-16 ignore cache-7 files
2021-11-02 migrate to codepod IDE
2021-11-02 add optional to make-circuit
2021-11-02 remove extra global def
2021-11-02 rename make-circuit0
2021-11-02 remote outputs from (require bhdl)
2021-11-04 run through placement
2021-11-04 support detect cpu&gpu
2021-11-05 use deck's name as NS and dir
2021-11-05 add julia export; add CP_CONFIG
2021-11-05 add julia deps manually
2021-11-05 add Reexport
2021-11-06 make julia export working
2021-11-06 clean up README
2021-12-06 adjust .pods format for codepod local
2022-01-01 support functional syntax
2022-02-18 add setup instructions
2022-02-18 change :::note to quote
2022-02-18 change one more ::: note to quote
